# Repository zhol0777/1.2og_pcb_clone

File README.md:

# 1.2og repro pcb

| front                           | back                          | lightbar                  |
| --------------------------------- | --------------------------- | ------------------------- |
|  |  |  |

unfinished attempt to re-create pcb and lightbar for matrix 1.2og.

this has been designed by using pcb edge cuts and plate file that were provided courtesy of astro of matrixlab [here](https://geekhack.org/index.php?topic=106122.msg2901076#msg2901076). without it, re-creating the PCB would be a more maddening and expensive experience. it has 19.02mm x 19.02mm spacing (mostly). 

indicator LEDs on scroll lock and caps lock. JST headers are for s3b ph 3 pin, since that's what it looks like from watching youtube build videos.

## warnings/differences

* The official plate file is treated as the source of truth for where switches should be placed
  * The official 1.2OG PCB edge cuts provided by astro has some arcane spacing rules -
    * 19.02mm on y axis for every row
    * 19.02mm on x axis on first three rows and all arrow keys
    * 19.00mm on row 4 on the main cluster of keys (not arrow keys)
      * The right shift key might still be at where it would be at 19.02mm spacing. The left shift key, i'm not sure, I just placed it where it would have been at 19.02mm spacing.
    * 18.978mmm on modifier keys in the bottom row (not sure if spacebar key is affected)
  * all of this is ignored in favor of sticking with plate dimensions or expected plate dimensions, which are 19.02mm x 19.02mm spacing, EXCEPT
    * 19.024mm y-axis spacing between the function row and regular key cluster
    * the distance between the `M` and `Comma` key is 19.03mm.
* lightbar mounting holes on PCB are slightly off-spec, and in here are plated m3 (edge cuts seem to imply the hole is a bit wider).
* lightbar can now connected to PCB through a molex pico ezmate cable. if you don't like it, you can assemble without it, and solder the s3b connector on yourself.
  * https://www.mouser.com/ProductDetail/Molex/36920-0301 - pick these up, and cut them down the middle to solder wires direct to lightbar
* split backspace and split right shift are included, in case anyone is wants to make a plate that supports those switches. ISO left shift and enter are not included due to laziness.
* usb port placement is mostly guessing.
* 6U spacebar support is added because I miss using my hhkb pro 2.

## misc, thanks

stm32f072 schematic is courtesy of xphoenixd. thanks for teaching me how to design PCB's, man. schematic for ws2812c-2020 rgb chain is inspired by zykrah's [fuyu](https://github.com/zykrah/fuyu). voltage step-up thing for lightbar is inspired by schematic from fuyu and dededecline and olivia's [sst60](https://github.com/dededecline/SST60).

an earlier revision included a basic reset circuit provided by xyz, who also pointed out an issue in the BOM that caused one major issue with the first round of prototypes - were it not for him, I'd probably make two more rounds of protos with the same issue. all love to matthewdias, islandworks, and mel for pointing out a glaring issue with USB, and doubly so for matt for being willing to replace 0402 package resistors pro bono after xyz pointed out how a BOM mistake from me rendered the reset circuit useless. thanks to chippy, phoenix, and chill for misc. advice on how to design this.

i don't know if i'm allowed to license this, given the pcb edge cuts this is based off of were released without a license. nevertheless, they were provided by astro from matrixlab. thank you!

no working prototype has been made for this yet! beware!

## todo
1. ~~fill out BOM real good~~
2. measure and source standoffs that are good enough and ultra low profile screws
3. ~~split main pcb and lightbar pcb separately so jlcpcb production files don't keep bothering each other~~
4. adjust placement of ws2812 based on if it is too far to one side of the lightbar or the other.
5. consider alternative to ws2812 2020 if power consumption/cost reasons.
6. prototype PCB and lightbar
7. ~~firmware (come on, this is basically automated at this point)~~
8. modify lightbar to support both direct soldering and ezmate/jst ach through mouse bite/break off thing or something
  * i think there should be straight ezmate to this, it would make peoples lives so much easier (ignoring how you'd route the extra cable slack)
9. verify this works with original lightbar

## prototyping progress

first revision (in beta branch) failed due to rookie mistake of using USB symbol from one library and footprint from another - the pins between each were in reverse order of each other, which made the prototype useless. whoops! after shipping PCBs to matt for rework, some goons looked over this in kicad pcbeditor and pointed out that the pins over USB were in reverse order.

second prototype arrived 5.31.2023, and exhibited strange behavior - on boot to bootloader mode, dfu-util is able to flash the PCB seemingly fine, and then after reset, the PCB appears recognized by VIAL, at which point **every single device connected over the same USB hub** goes unresponsive. the pcb is also unresponsive. five seconds pass, the PCB dissapears from VIAL, and USB devices begin working again. something deeply bad has happened, so I've tried rearranging all the parts, validating BOM, and praying next revision works.

the latest push to main branch uses molex 0548190519, which I haven't prototyped, but shouldn't be too different otherwise.

i've bought these SMT M2 threaded spacer/standoffs so that lightbar can mount to pcb - https://www.mouser.com/ProductDetail/Wurth-Elektronik/9774015243R - you're probably supposed to use solder paste to assemble these things, but I don't have that, so I don't know, maybe I'll use solder shavings to get these things soldered on. they're slightly smaller than the m3 plated hole on pcb/lightbar, but I don't think it'll matter too much, since they should align one way or another.

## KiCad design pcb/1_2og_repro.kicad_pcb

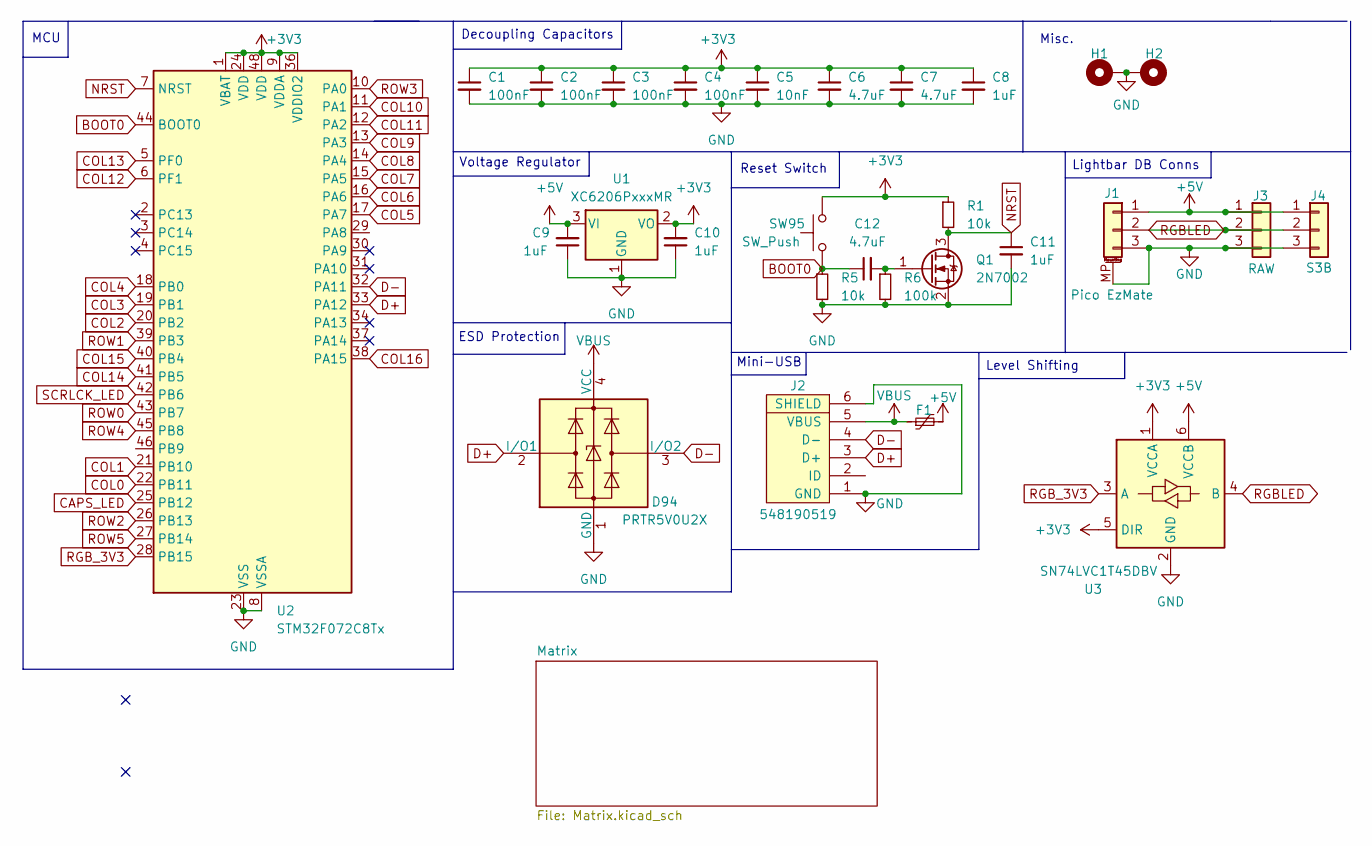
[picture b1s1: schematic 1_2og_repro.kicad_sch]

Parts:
C1, C2, C3, C4: 100nF; C_0402_1005Metric
C5: 10nF; C_0402_1005Metric
C6, C7, C12: 4.7uF; C_0402_1005Metric
C8, C9, C10, C11: 1uF; C_0402_1005Metric
D94: PRTR5V0U2X; SOT-143
F1: 500mA; Fuse_1206_3216Metric
H1, H2: MountingHole_Pad; MountingHole_3mm_Pad
J1: Pico EzMate; Molex_Pico-EZmate_78171-0003_1x03-1MP_P1.20mm_Vertical
J2: 548190519; Molex-0548190519
J3: RAW; PinHeader_1x03_P2.54mm_Vertical
J4: S3B; JST_PH_S3B-PH-K_1x03_P2.00mm_Horizontal
Q1: 2N7002; SOT-23
R1, R5: 10k; R_0402_1005Metric
R6: 100k; R_0402_1005Metric
SW95: SW_Push; SW_SPST_TL3342
U1: XC6206PxxxMR; SOT-23
U2: STM32F072C8Tx; LQFP-48_7x7mm_P0.5mm
U3: SN74LVC1T45DBV; SOT-23-6

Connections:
+3V3: C1.1, C2.1, C3.1, C4.1, C5.1, C6.1, C7.1, C8.1, C10.2, R1.1, SW95.2, U1.2 (VO), U2.1 (VBAT), U2.9 (VDDA), U2.24 (VDD), U2.36 (VDDIO2), U2.48 (VDD), U3.1 (VCCA), U3.5 (DIR)
+5V: C9.2, F1.2, J1.1, J3.1, J4.1, U1.3 (VI), U3.6 (VCCB)
BOOT0: C12.1, R5.1, SW95.1, U2.44 (BOOT0)
CAPS_LED: U2.25 (PB12); also elsewhere on the board
COL0: U2.22 (PB11); also elsewhere on the board
COL1: U2.21 (PB10); also elsewhere on the board
COL2: U2.20 (PB2); also elsewhere on the board
COL3: U2.19 (PB1); also elsewhere on the board
COL4: U2.18 (PB0); also elsewhere on the board
COL5: U2.17 (PA7); also elsewhere on the board
COL6: U2.16 (PA6); also elsewhere on the board
COL7: U2.15 (PA5); also elsewhere on the board
COL8: U2.14 (PA4); also elsewhere on the board
COL9: U2.13 (PA3); also elsewhere on the board
COL10: U2.11 (PA1); also elsewhere on the board
COL11: U2.12 (PA2); also elsewhere on the board
COL12: U2.6 (PF1); also elsewhere on the board
COL13: U2.5 (PF0); also elsewhere on the board
COL14: U2.41 (PB5); also elsewhere on the board
COL15: U2.40 (PB4); also elsewhere on the board
COL16: U2.38 (PA15); also elsewhere on the board
D+: D94.2 (I/O1), J2.3 (D+), U2.33 (PA12)
D-: D94.3 (I/O2), J2.4 (D-), U2.32 (PA11)
GND: C1.2, C2.2, C3.2, C4.2, C5.2, C6.2, C7.2, C8.2, C9.1, C10.1, C11.2, D94.1 (GND), H1.1, H2.1, J1.3, J1.MP (MountPin), J2.1 (GND), J2.6 (SHIELD), J3.3, J4.3, Q1.2 (S), R5.2, R6.2, U1.1 (GND), U2.8 (VSSA), U2.23 (VSS), U2.35 (VSS), U2.47 (VSS), U3.2 (GND); also elsewhere on the board
NRST: C11.1, Q1.3 (D), R1.2, U2.7 (NRST)
unnamed: C12.2, Q1.1 (G), R6.1
RGBLED: J1.2, J3.2, J4.2, U3.4 (B)
RGB_3V3: U2.28 (PB15), U3.3 (A)
ROW0: U2.43 (PB7); also elsewhere on the board
ROW1: U2.39 (PB3); also elsewhere on the board
ROW2: U2.26 (PB13); also elsewhere on the board
ROW3: U2.10 (PA0); also elsewhere on the board
ROW4: U2.45 (PB8); also elsewhere on the board
ROW5: U2.27 (PB14); also elsewhere on the board
SCRLCK_LED: U2.42 (PB6); also elsewhere on the board
VBUS: D94.4 (VCC), F1.1, J2.5 (VBUS)

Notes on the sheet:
Level Shifting
Mini-USB
Reset Switch
MCU
ESD Protection
Voltage Regulator
Misc.
Lightbar DB Conns
Decoupling Capacitors

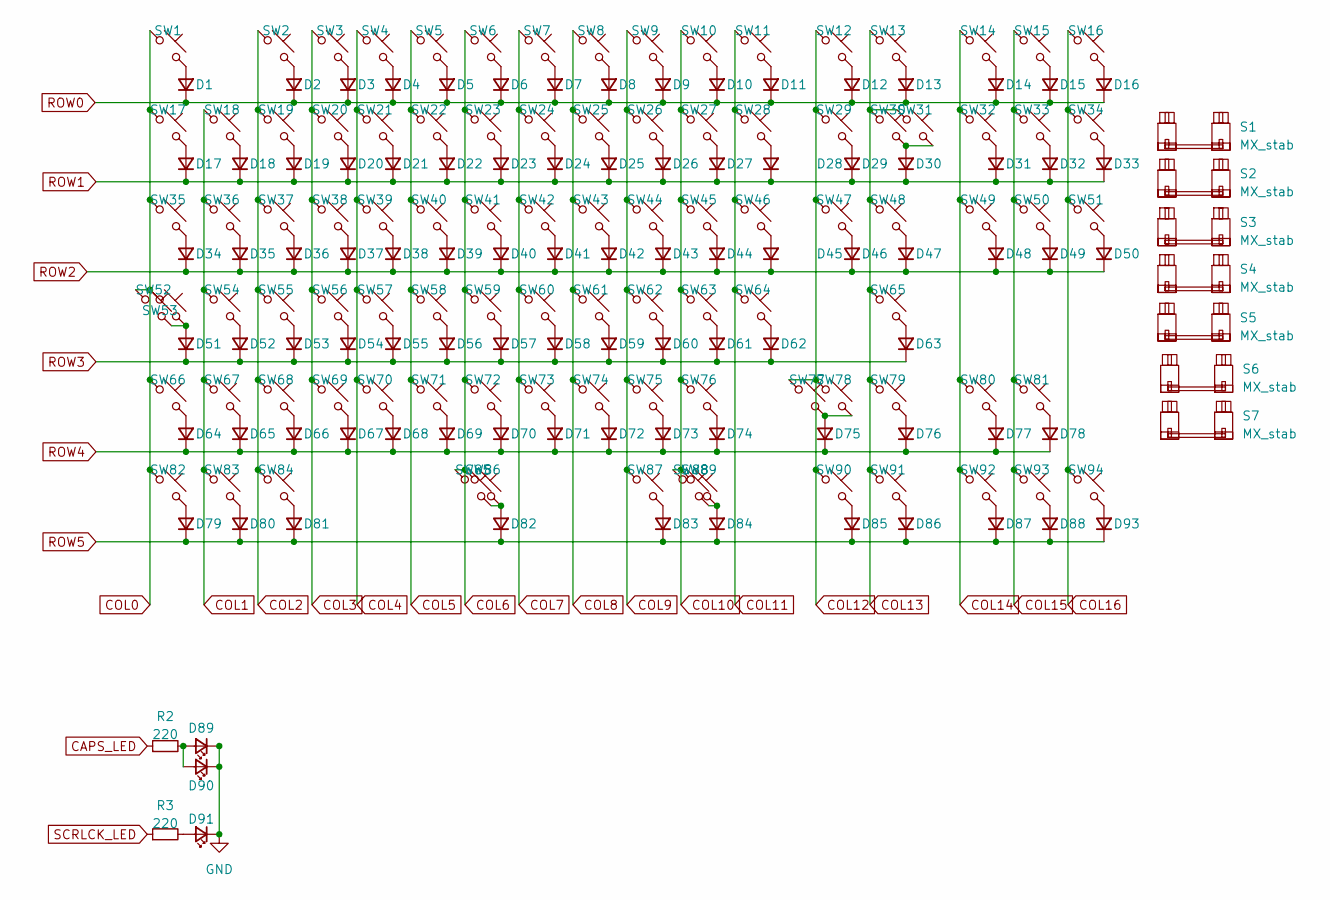
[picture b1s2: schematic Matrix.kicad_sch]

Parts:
D1, D2, D3, D4, D5, D6, D7, D8, D9, D10, D11, D12, D13, D14, D15, D16, D17, D18, D19, D20, D21, D22, D23, D24, D25, D26, D27, D28, D29, D30, D31, D32, D33, D34, D35, D36, D37, D38, D39, D40, D41, D42, D43, D44, D45, D46, D47, D48, D49, D50, D51, D52, D53, D54, D55, D56, D57, D58, D59, D60, D61, D62, D63, D64, D65, D66, D67, D68, D69, D70, D71, D72, D73, D74, D75, D76, D77, D78, D79, D80, D81, D82, D83, D84, D85, D86, D87, D88, D93: D_Small; D_SOD-123
D89, D91: LED_Small; LED_MX_3mm
D90: LED_Small; LED_MX_3mm-ROT
R2, R3: 220; R_0402_1005Metric
S1: MX_stab; STAB_MX_P_2u
S2, S3: MX_stab; STAB_MX_2.25u
S4: MX_stab; STAB_MX_P_2.75u
S5: MX_stab; STAB_MX_7u
S6: MX_stab; STAB_MX_6u
S7: MX_stab; STAB_MX_10u
SW1, SW2, SW3, SW4, SW5, SW6, SW7, SW8, SW9, SW10, SW11, SW12, SW13, SW14, SW15, SW16, SW17, SW18, SW19, SW20, SW21, SW22, SW23, SW24, SW25, SW26, SW27, SW28, SW29, SW30, SW31, SW32, SW33, SW34, SW36, SW37, SW38, SW39, SW40, SW41, SW42, SW43, SW44, SW45, SW46, SW47, SW49, SW50, SW51, SW54, SW55, SW56, SW57, SW58, SW59, SW60, SW61, SW62, SW63, SW64, SW65, SW66, SW67, SW68, SW69, SW70, SW71, SW72, SW73, SW74, SW75, SW76, SW78, SW79, SW80, SW81, SW83, SW85, SW86, SW88, SW90, SW92, SW93, SW94: MX_SW_solder; SW_MX_1u
SW35, SW48, SW82, SW84, SW87, SW89, SW91: MX_SW_solder; SW_MX_1.5u
SW52: MX_SW_solder; SW_MX_1.75u_STP_1.25
SW53, SW77: MX_SW_solder; SW_MX_1.75u

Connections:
CAPS_LED: R2.1; also elsewhere on the board
COL0: SW1.1, SW17.1, SW35.1, SW52.1, SW53.1, SW66.1, SW82.1; also elsewhere on the board
COL1: SW18.1, SW36.1, SW54.1, SW67.1, SW83.1; also elsewhere on the board
COL2: SW2.1, SW19.1, SW37.1, SW55.1, SW68.1, SW84.1; also elsewhere on the board
COL3: SW3.1, SW20.1, SW38.1, SW56.1, SW69.1; also elsewhere on the board
COL4: SW4.1, SW21.1, SW39.1, SW57.1, SW70.1; also elsewhere on the board
COL5: SW5.1, SW22.1, SW40.1, SW58.1, SW71.1; also elsewhere on the board
COL6: SW6.1, SW23.1, SW41.1, SW59.1, SW72.1, SW85.1, SW86.1; also elsewhere on the board
COL7: SW7.1, SW24.1, SW42.1, SW60.1, SW73.1; also elsewhere on the board
COL8: SW8.1, SW25.1, SW43.1, SW61.1, SW74.1; also elsewhere on the board
COL9: SW9.1, SW26.1, SW44.1, SW62.1, SW75.1, SW87.1; also elsewhere on the board
COL10: SW10.1, SW27.1, SW45.1, SW63.1, SW76.1, SW88.1, SW89.1; also elsewhere on the board
COL11: SW11.1, SW28.1, SW46.1, SW64.1; also elsewhere on the board
COL12: SW12.1, SW29.1, SW47.1, SW77.1, SW78.1, SW90.1; also elsewhere on the board
COL13: SW13.1, SW30.1, SW31.1, SW48.1, SW65.1, SW79.1, SW91.1; also elsewhere on the board
COL14: SW14.1, SW32.1, SW49.1, SW80.1, SW92.1; also elsewhere on the board
COL15: SW15.1, SW33.1, SW50.1, SW81.1, SW93.1; also elsewhere on the board
COL16: SW16.1, SW34.1, SW51.1, SW94.1; also elsewhere on the board
GND: D89.1 (K), D90.1 (K), D91.1 (K); also elsewhere on the board
unnamed: D1.2 (A), SW1.2
unnamed: D2.2 (A), SW2.2
unnamed: D3.2 (A), SW3.2
unnamed: D4.2 (A), SW4.2
unnamed: D5.2 (A), SW5.2
unnamed: D6.2 (A), SW6.2
unnamed: D7.2 (A), SW7.2
unnamed: D8.2 (A), SW8.2
unnamed: D9.2 (A), SW9.2
unnamed: D10.2 (A), SW10.2
unnamed: D11.2 (A), SW11.2
unnamed: D12.2 (A), SW12.2
unnamed: D13.2 (A), SW13.2
unnamed: D14.2 (A), SW14.2
unnamed: D15.2 (A), SW15.2
unnamed: D16.2 (A), SW16.2
unnamed: D17.2 (A), SW17.2
unnamed: D18.2 (A), SW18.2
unnamed: D19.2 (A), SW19.2
unnamed: D20.2 (A), SW20.2
unnamed: D21.2 (A), SW21.2
unnamed: D22.2 (A), SW22.2
unnamed: D23.2 (A), SW23.2
unnamed: D24.2 (A), SW24.2
unnamed: D25.2 (A), SW25.2
unnamed: D26.2 (A), SW26.2
unnamed: D27.2 (A), SW27.2
unnamed: D28.2 (A), SW28.2
unnamed: D29.2 (A), SW29.2
unnamed: D30.2 (A), SW30.2, SW31.2
unnamed: D31.2 (A), SW32.2
unnamed: D32.2 (A), SW33.2
unnamed: D33.2 (A), SW34.2
unnamed: D34.2 (A), SW35.2
unnamed: D35.2 (A), SW36.2
unnamed: D36.2 (A), SW37.2
unnamed: D37.2 (A), SW38.2
unnamed: D38.2 (A), SW39.2
unnamed: D39.2 (A), SW40.2
unnamed: D40.2 (A), SW41.2
unnamed: D41.2 (A), SW42.2
unnamed: D42.2 (A), SW43.2
unnamed: D43.2 (A), SW44.2
unnamed: D44.2 (A), SW45.2
unnamed: D45.2 (A), SW46.2
unnamed: D46.2 (A), SW47.2
unnamed: D47.2 (A), SW48.2
unnamed: D48.2 (A), SW49.2
unnamed: D49.2 (A), SW50.2
unnamed: D50.2 (A), SW51.2
unnamed: D51.2 (A), SW52.2, SW53.2
unnamed: D52.2 (A), SW54.2
unnamed: D53.2 (A), SW55.2
unnamed: D54.2 (A), SW56.2
unnamed: D55.2 (A), SW57.2
unnamed: D56.2 (A), SW58.2
unnamed: D57.2 (A), SW59.2
unnamed: D58.2 (A), SW60.2
unnamed: D59.2 (A), SW61.2
unnamed: D60.2 (A), SW62.2
unnamed: D61.2 (A), SW63.2
unnamed: D62.2 (A), SW64.2
unnamed: D63.2 (A), SW65.2
unnamed: D64.2 (A), SW66.2
unnamed: D65.2 (A), SW67.2
unnamed: D66.2 (A), SW68.2
unnamed: D67.2 (A), SW69.2
unnamed: D68.2 (A), SW70.2
unnamed: D69.2 (A), SW71.2
unnamed: D70.2 (A), SW72.2
unnamed: D71.2 (A), SW73.2
unnamed: D72.2 (A), SW74.2
unnamed: D73.2 (A), SW75.2
unnamed: D74.2 (A), SW76.2
unnamed: D75.2 (A), SW77.2, SW78.2
unnamed: D76.2 (A), SW79.2
unnamed: D77.2 (A), SW80.2
unnamed: D78.2 (A), SW81.2
unnamed: D79.2 (A), SW82.2
unnamed: D80.2 (A), SW83.2
unnamed: D81.2 (A), SW84.2
unnamed: D82.2 (A), SW85.2, SW86.2
unnamed: D83.2 (A), SW87.2
unnamed: D84.2 (A), SW88.2, SW89.2
unnamed: D85.2 (A), SW90.2
unnamed: D86.2 (A), SW91.2
unnamed: D87.2 (A), SW92.2
unnamed: D88.2 (A), SW93.2
unnamed: D89.2 (A), D90.2 (A), R2.2
unnamed: D91.2 (A), R3.2
unnamed: D93.2 (A), SW94.2
ROW0: D1.1 (K), D2.1 (K), D3.1 (K), D4.1 (K), D5.1 (K), D6.1 (K), D7.1 (K), D8.1 (K), D9.1 (K), D10.1 (K), D11.1 (K), D12.1 (K), D13.1 (K), D14.1 (K), D15.1 (K), D16.1 (K); also elsewhere on the board
ROW1: D17.1 (K), D18.1 (K), D19.1 (K), D20.1 (K), D21.1 (K), D22.1 (K), D23.1 (K), D24.1 (K), D25.1 (K), D26.1 (K), D27.1 (K), D28.1 (K), D29.1 (K), D30.1 (K), D31.1 (K), D32.1 (K), D33.1 (K); also elsewhere on the board
ROW2: D34.1 (K), D35.1 (K), D36.1 (K), D37.1 (K), D38.1 (K), D39.1 (K), D40.1 (K), D41.1 (K), D42.1 (K), D43.1 (K), D44.1 (K), D45.1 (K), D46.1 (K), D47.1 (K), D48.1 (K), D49.1 (K), D50.1 (K); also elsewhere on the board
ROW3: D51.1 (K), D52.1 (K), D53.1 (K), D54.1 (K), D55.1 (K), D56.1 (K), D57.1 (K), D58.1 (K), D59.1 (K), D60.1 (K), D61.1 (K), D62.1 (K), D63.1 (K); also elsewhere on the board
ROW4: D64.1 (K), D65.1 (K), D66.1 (K), D67.1 (K), D68.1 (K), D69.1 (K), D70.1 (K), D71.1 (K), D72.1 (K), D73.1 (K), D74.1 (K), D75.1 (K), D76.1 (K), D77.1 (K), D78.1 (K); also elsewhere on the board
ROW5: D79.1 (K), D80.1 (K), D81.1 (K), D82.1 (K), D83.1 (K), D84.1 (K), D85.1 (K), D86.1 (K), D87.1 (K), D88.1 (K), D93.1 (K); also elsewhere on the board
SCRLCK_LED: R3.1; also elsewhere on the board

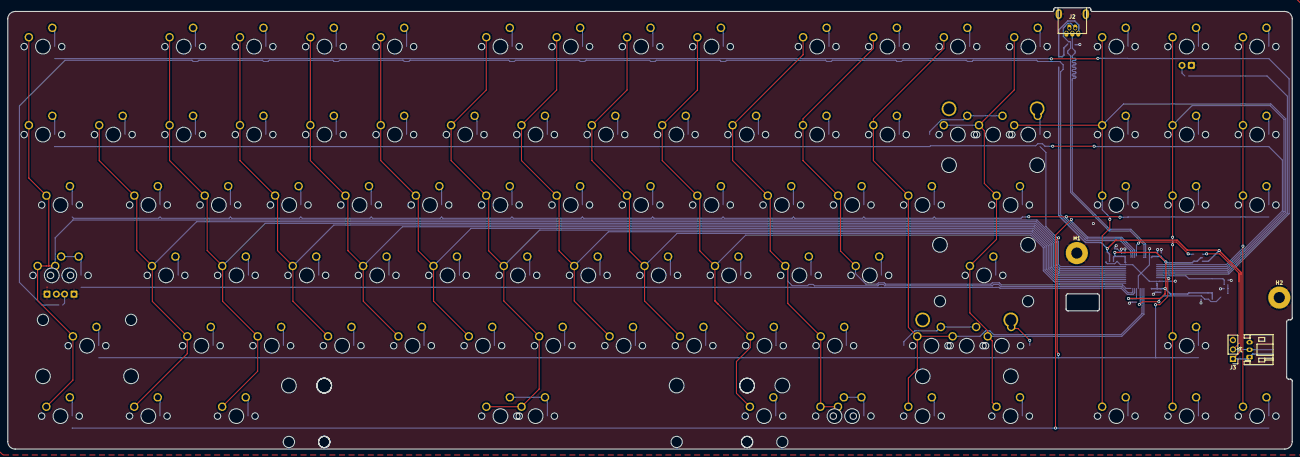
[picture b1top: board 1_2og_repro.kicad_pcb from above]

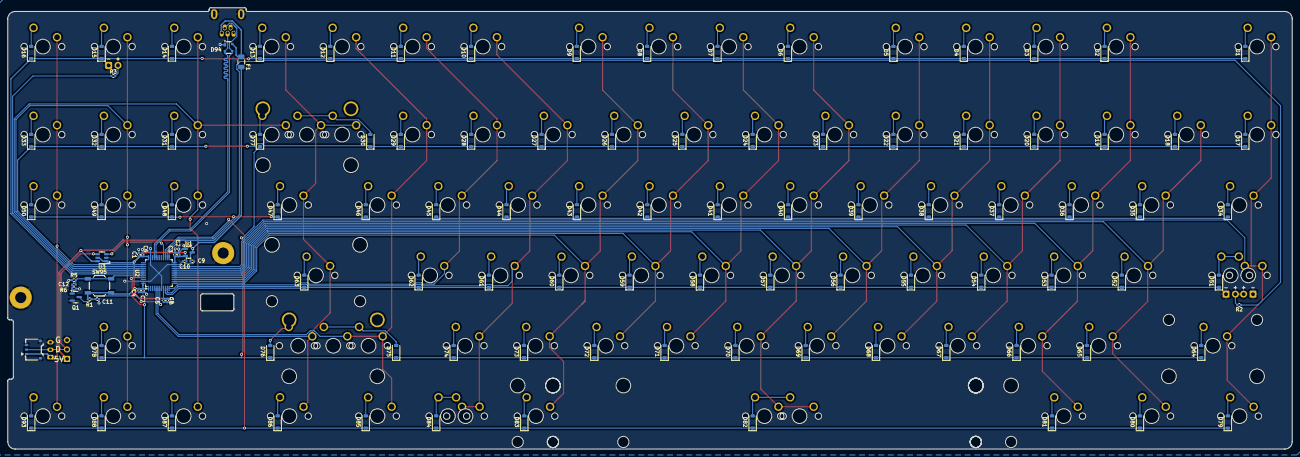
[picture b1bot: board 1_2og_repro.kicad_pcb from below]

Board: 2 copper layers, 347.1 x 119.3 mm, 223 parts (115 on the bottom side), 127 nets.

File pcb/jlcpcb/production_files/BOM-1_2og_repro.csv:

Comment,Designator,Footprint,LCSC,Quantity
10nF,C5,C_0402_1005Metric,C15195,1
100nF,"C1,C2,C3,C4",C_0402_1005Metric,C1525,4
S3B,J4,JST_PH_S3B-PH-K_1x03_P2.00mm_Horizontal,C157929,1
4.7uF,"C12,C6,C7",C_0402_1005Metric,C23733,3
548190519,J2,Molex-0548190519,C240850,1
220,"R2,R3",R_0402_1005Metric,C25091,2
100k,R6,R_0402_1005Metric,C25741,1
10k,"R1,R5",R_0402_1005Metric,C25744,2
PRTR5V0U2X,D94,SOT-143,C2827688,1
Pico EzMate,J1,Molex_Pico-EZmate_78171-0003_1x03-1MP_P1.20mm_Vertical,C2997426,1
SW_Push,SW95,SW_SPST_TL3342,C318884,1
1uF,"C10,C11,C8,C9",C_0402_1005Metric,C52923,4
XC6206PxxxMR,U1,SOT-23,C5446,1
SN74LVC1T45DBV,U3,SOT-23-6-routable,C7843,1
D_Small,"D1,D10,D11,D12,D13,D14,D15,D16,D17,D18,D19,D2,D20,D21,D22,D23,D24,D25,D26,D27,D28,D29,D3,D30,D31,D32,D33,D34,D35,D36,D37,D38,D39,D4,D40,D41,D42,D43,D44,D45,D46,D47,D48,D49,D5,D50,D51,D52,D53,D54,D55,D56,D57,D58,D59,D6,D60,D61,D62,D63,D64,D65,D66,D67,D68,D69,D7,D70,D71,D72,D73,D74,D75,D76,D77,D78,D79,D8,D80,D81,D82,D83,D84,D85,D86,D87,D88,D9,D93",D_SOD-123,C81598,89
STM32F072C8Tx,U2,LQFP-48_7x7mm_P0.5mm,C81720,1
2N7002,Q1,SOT-23,C8545,1
500mA,F1,Fuse_1206_3216Metric,C883122,1

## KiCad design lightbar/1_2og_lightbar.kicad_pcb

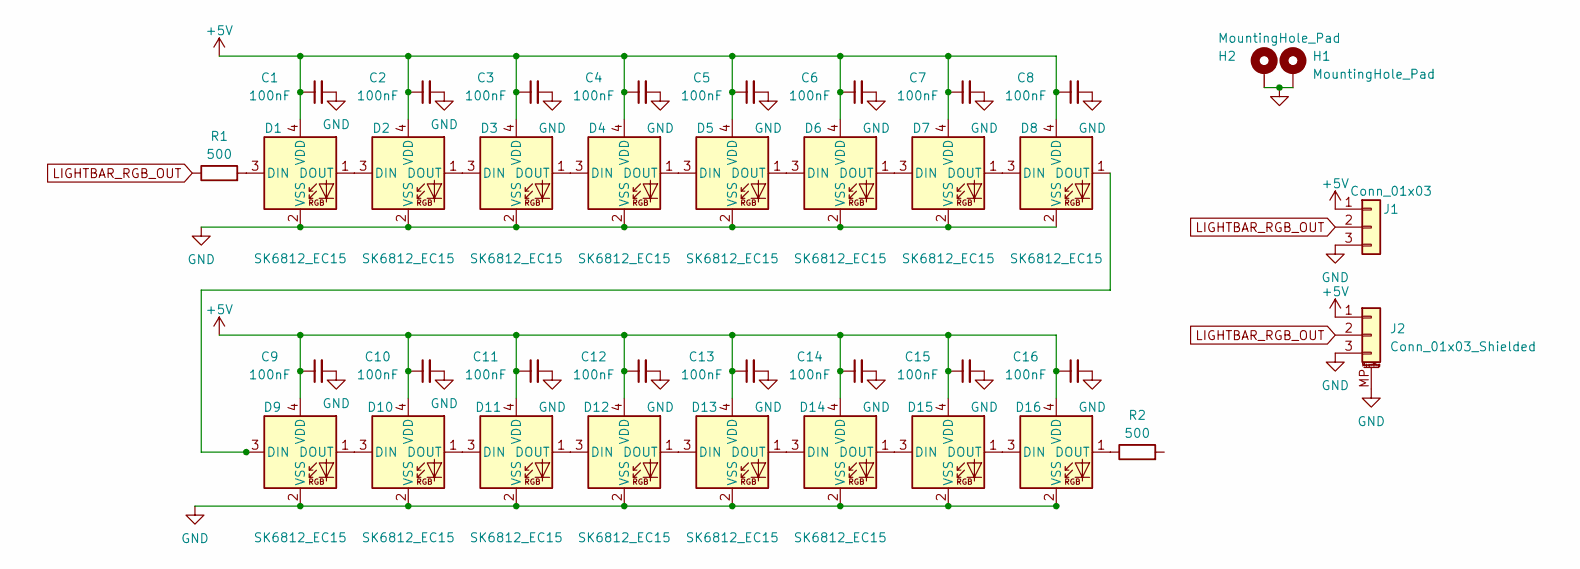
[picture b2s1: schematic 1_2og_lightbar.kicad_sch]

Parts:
C1, C2, C3, C4, C5, C6, C7, C8, C9, C10, C11, C12, C13, C14, C15, C16: 100nF; C_0402_1005Metric
D1, D2, D3, D4, D5, D6, D7, D8, D9, D10, D11, D12, D13, D14, D15, D16: SK6812_EC15; LED_SK6812_EC15_1.5x1.5mm
H1, H2: MountingHole_Pad; MountingHole_3mm_Pad
J1: Conn_01x03; PinHeader_1x03_P2.54mm_Vertical
J2: Conn_01x03_Shielded; Molex_Pico-EZmate_78171-0003_1x03-1MP_P1.20mm_Vertical
R1, R2: 500; R_0805_2012Metric

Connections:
+5V: C1.1, C2.1, C3.1, C4.1, C5.1, C6.1, C7.1, C8.1, C9.1, C10.1, C11.1, C12.1, C13.1, C14.1, C15.1, C16.1, D1.4 (VDD), D2.4 (VDD), D3.4 (VDD), D4.4 (VDD), D5.4 (VDD), D6.4 (VDD), D7.4 (VDD), D8.4 (VDD), D9.4 (VDD), D10.4 (VDD), D11.4 (VDD), D12.4 (VDD), D13.4 (VDD), D14.4 (VDD), D15.4 (VDD), D16.4 (VDD), J1.1, J2.1
GND: C1.2, C2.2, C3.2, C4.2, C5.2, C6.2, C7.2, C8.2, C9.2, C10.2, C11.2, C12.2, C13.2, C14.2, C15.2, C16.2, D1.2 (VSS), D2.2 (VSS), D3.2 (VSS), D4.2 (VSS), D5.2 (VSS), D6.2 (VSS), D7.2 (VSS), D8.2 (VSS), D9.2 (VSS), D10.2 (VSS), D11.2 (VSS), D12.2 (VSS), D13.2 (VSS), D14.2 (VSS), D15.2 (VSS), D16.2 (VSS), H1.1, H2.1, J1.3, J2.3, J2.MP (MountPin)
LIGHTBAR_RGB_OUT: J1.2, J2.2, R1.1
unnamed: D1.3 (DIN), R1.2
unnamed: D1.1 (DOUT), D2.3 (DIN)
unnamed: D2.1 (DOUT), D3.3 (DIN)
unnamed: D3.1 (DOUT), D4.3 (DIN)
unnamed: D4.1 (DOUT), D5.3 (DIN)
unnamed: D5.1 (DOUT), D6.3 (DIN)
unnamed: D6.1 (DOUT), D7.3 (DIN)
unnamed: D7.1 (DOUT), D8.3 (DIN)
unnamed: D8.1 (DOUT), D9.3 (DIN)
unnamed: D9.1 (DOUT), D10.3 (DIN)
unnamed: D10.1 (DOUT), D11.3 (DIN)
unnamed: D11.1 (DOUT), D12.3 (DIN)
unnamed: D12.1 (DOUT), D13.3 (DIN)
unnamed: D13.1 (DOUT), D14.3 (DIN)
unnamed: D14.1 (DOUT), D15.3 (DIN)
unnamed: D15.1 (DOUT), D16.3 (DIN)
unnamed: D16.1 (DOUT), R2.1

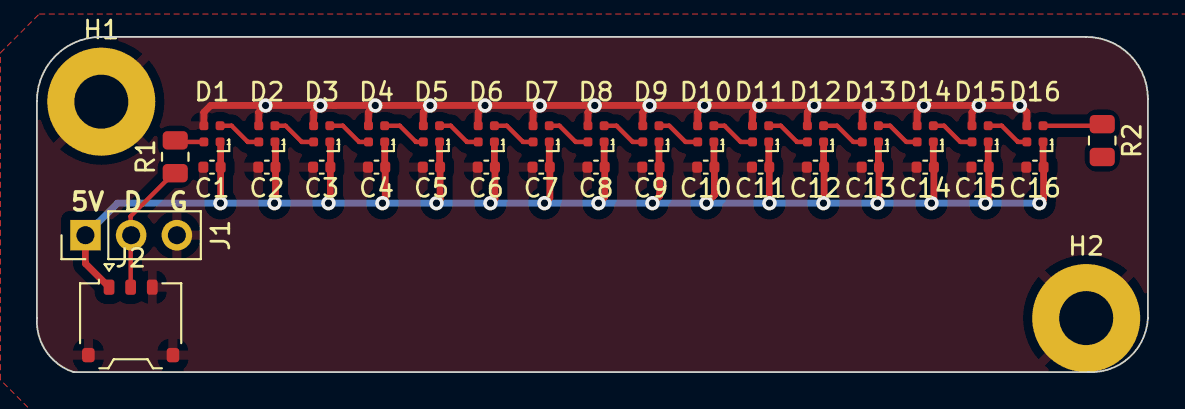
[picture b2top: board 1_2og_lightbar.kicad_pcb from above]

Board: 2 copper layers, 61.7 x 18.6 mm, 38 parts (0 on the bottom side), 20 nets.

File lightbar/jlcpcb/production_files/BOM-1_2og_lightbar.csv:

Comment,Designator,Footprint,LCSC,Quantity
100nF,"C1,C10,C11,C12,C13,C14,C15,C16,C2,C3,C4,C5,C6,C7,C8,C9",C_0402_1005Metric,C1525,16
500,"R1,R2",R_0805_2012Metric,C2828711,2
SK6812_EC15,"D1,D10,D11,D12,D13,D14,D15,D16,D2,D3,D4,D5,D6,D7,D8,D9",LED_SK6812_EC15_1.5x1.5mm,C2890035,16
Conn_01x03_Shielded,J2,Molex_Pico-EZmate_78171-0003_1x03-1MP_P1.20mm_Vertical,C2997426,1

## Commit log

2023-05-05 init
2023-05-05 add lightbar kinda (gerbers have not been fully updated yet, bom is broken)
2023-05-05 dual jst-ph and ezmate support on pcb
2023-05-05 reorganizing, re-do BOM
2023-05-05 routing improvements
2023-05-06 spacing updates, silkscreens and etc
2023-05-06 fix 3v3 connections to mcu
2023-05-07 re-route pcb
2023-05-07 firmware
2023-05-07 do not use PB2 as column pin
2023-05-08 redo reset circuit component placement, fix bottom row spacing with 19.03mm weird thing
2023-05-18 remove obnoxious back silkscreen appearing by default
2023-05-19 fix BOM
2023-05-19 simplify
2023-05-22 fix usb pin symbol footpring mixup
2023-05-31 add 6u support (firmware does not reflect this yet), usb 0548190519
    previous USB is annoying to hand-solder without wick, using through-hole
    pins may be less of a pain. 6u support is added because I miss my HHKB.
2023-05-31 add credit
2023-07-03 REMAKE - FIRMWARE NEEDS UPDATES
2023-07-07 firmware update
2023-07-07 update gerbers, change mounting hole dimensions
2023-07-07 ok juggle a few pins around
2023-07-08 tune differential pair, reroute to remove redundant vias
2025-02-22 remove unncessary file?
2025-02-23 sunday at the waterpark
